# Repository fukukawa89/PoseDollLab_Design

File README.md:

# PoseDoll 人偶硬件设计

通用静态测姿人偶的独立设计仓库；Manny / Quinn 为软件适配目标。原来位于 `DollSimulation` UE 工程中的硬件、固件与硬件诊断工具已经迁入本目录；UE 插件、角色资产与完整 Python 模拟器留在原项目。

## 当前状态

**2026-10-30 O24E 单臂 R5：七自由度测角升级。** 以用户已实装认可摩擦与持姿效果的 R4 为基线，复用六路 O22 MT6701CT 与七颗径向充磁磁铁，腕偏摆增加一路 TMAG5170A1，双轴腕分别测量。保留 R4 摩擦、预紧、防脱结构及 136 件机械五金；重印 P005、P007、P009、P010、P012，复用其余六件主体，新增 29 件传感器附件及 J003/J004 工具。交付打印工程、清单、走线、409 步装配动画、固件和标定工具。数字几何、装配、切片、浏览器与软件检查通过；R5 实物测角精度、走线和升级后的持姿仍待测试，未烧录硬件。

- [R5 打印与装配入口](Hardware/PoseDoll44/bench/revO24E_LArm_Sensing_R5/START_HERE.html) · [重印说明](Hardware/PoseDoll44/bench/revO24E_LArm_Sensing_R5/PRINTING.html)
- [R5 测角方案](Hardware/PoseDoll44/bench/revO24E_LArm_Sensing_R5/SENSING.html) · [逐步装配动画](Hardware/PoseDoll44/bench/revO24E_LArm_Sensing_R5/assembly_guide/index.html) · [验证记录](Hardware/PoseDoll44/bench/revO24E_LArm_Sensing_R5/VERIFICATION.html)
- [R5 完整离线包](Hardware/PoseDoll44/bench/revO24E_LArm_Sensing_R5/O24E_R5_Arm_Sensing_20261030.zip) · [R4 实装反馈](Hardware/PoseDoll44/docs/R4_MECHANICAL_FEEDBACK_20261030.json)

**2026-10-26 O24D 改版交接：** 用户满意当前 O24D 外观，后续保留外观与 UE 骨架，重点重做关节连接、预紧、防松、防脱及装配。T6 W 按用户实装反馈通过；T6 H 按用户依据 T5 安装和 T6 继承关系的判断接受通过，可用于设计推进。T6 R 的整组轴向拔出是已确认缺陷，必须修复。当前 D 的 20 组金属筒输出套还存在规定装入路径与横销干涉，旧球腕入口及机构也需更新。[完整经验、审查与新对话任务](Hardware/PoseDoll44/docs/HANDOFF_O24D_REDESIGN_20261026.zh-CN.md)。本次仅整理与审查，未改动 D/T6 冻结交付包；100 次不补紧目标保留，不虚构循环数据。

**O24C-T6：尼龙锁母防松测试版（以下为发布记录，最新实物反馈见上）。** 针对 T5 H 肩钉逐渐旋退，H、R、双轴腕的七组肩钉统一改用 M3×0.5 DIN985 尼龙锁紧螺母。新一体固定座采用完整六角止转窝和轴向装入，调整内部金属垫圈堆叠，保留原 Φ4×8 / M3×6 肩钉、A8、运动件及 UE 轴心。必须重印 H6-01、R6-01、W6-01，建议先印 C6-01 试配片；其余 10 件打印件与 T5 字节相同。按已备齐 T5 计算，补齐 7 颗锁母、14 片 9×4.3×0.8 平垫和 7 片 7×3.2×0.5 平垫。数字装配、活动采样、切片和教程检查通过；100 次不补紧仍待实测。

- [O24C-T6：打印、装配与测试入口](Hardware/PoseDoll44/bench/revO24C_T6/START_HERE.html)
- [O24C-T6：H 35 步 / R 42 步 / W 74 步逐件动画](Hardware/PoseDoll44/bench/revO24C_T6/tutorial/index.html)
- [O24C-T6：三件重印工程](Hardware/PoseDoll44/bench/revO24C_T6/printing/REPRINT_T6_three_parts.3mf) · [锁母试配片](Hardware/PoseDoll44/bench/revO24C_T6/printing/FIT_T6_locknut_coupon.3mf)
- [O24C-T6：补购与复用清单](Hardware/PoseDoll44/bench/revO24C_T6/HARDWARE.html) · [100 次测试](Hardware/PoseDoll44/bench/revO24C_T6/TEST_PLAN.html)
- [O24C-T6：完整离线包](Hardware/PoseDoll44/bench/revO24C_T6/O24C-T6_print_and_assembly.zip)

**O24C-T5：一体承力座测试版。** 用户实物反馈确认 T3/T4 的 H 摩擦力可用，但 H3-01/02 接缝在强拧和反复摆动后张开。T5 将其合并为 H5-01，同时把 R 固定芯与双轴腕十字芯改成 R5-01、W5-01；五金从侧向导槽装入，保留原有摩擦堆叠和 UE 轴心。仅重印三件，其余 11 个打印件复用，无新增五金规格，省去八组合模五金。旧 H 的反馈仅为定性持姿认可，T5 结构、R/W、磨损和寿命仍需实测。

- [O24C-T5：打印、改动说明与实测](Hardware/PoseDoll44/bench/revO24C_T5/START_HERE.html)
- [O24C-T5：H 29 步 / R 39 步 / W 62 步逐件动画](Hardware/PoseDoll44/bench/revO24C_T5/tutorial/index.html)
- [O24C-T5：三个一体件重印工程](Hardware/PoseDoll44/bench/revO24C_T5/printing/REPRINT_T5_three_parts.3mf)
- [O24C-T5：完整 14 件一盘工程](Hardware/PoseDoll44/bench/revO24C_T5/printing/ALL_H_R_W_T5.3mf)
- [O24C-T5：完整离线包](Hardware/PoseDoll44/bench/revO24C_T5/O24C-T5_print_and_assembly.zip)

**T5 H 最新实测反馈：** 初始摩擦可用，但反复转动十几次后明显衰减。使用普通螺母、没有额外锁固；追加观察发现内侧螺钉尖端从凸出变为缩进，重新拧入约两圈后恢复，强烈支持肩钉旋退为主要原因。当前状态未满足用户“至少活动100次无需补紧”的目标；优先完善独立防松，再验证剩余的沉降、磨损及摩擦变化。[实物反馈与改进要求](Hardware/PoseDoll44/docs/TEST_FEEDBACK_O24C_T5_H.zh-CN.md)。

**O24C-T4：双轴碟簧腕测试版。** 在T3实臂接口上，腕部改回相交双铰链：Y屈伸、随动X偏摆，分别用O22轴肩螺钉和A8预紧。只新增W4-01～04四个打印件；T3的H/R、W3-09掌柄、F3测试附件及C3试片原样复用。E—W仍为80.496305mm。T3球腕未实测，原文件保留供对比；T4持姿与磨损也待实测。新腕约39.6mm横向外廓，独立调摩擦的便利以宽度和更多五金为代价。

- [O24C-T4：打印、装配与五金增量](Hardware/PoseDoll44/bench/revO24C_T4/START_HERE.html)
- [O24C-T4：H 36 步 / R 46 步 / W 76 步逐件动画](Hardware/PoseDoll44/bench/revO24C_T4/tutorial/index.html)
- [已购早期 O22 + T1-S2：T3 / T4 补购对照](Hardware/PoseDoll44/bench/revO24C_T4/HARDWARE.html)
- [O24C-T4：三个样件共 17 件，一盘打印工程](Hardware/PoseDoll44/bench/revO24C_T4/printing/ALL_H_R_W_T4.3mf)
- [O24C-T4：双轴腕三维及逐件定位](Hardware/PoseDoll44/bench/revO24C_T4/viewer/index.html?mode=W)
- [O24C-T4：完整打印测试包](Hardware/PoseDoll44/bench/revO24C_T4/PoseDoll_O24C_T4_Dual_Axis_Wrist_Kit.zip)

**O24C-T3：可按实际骨长联装的肘 H、前臂旋转 R、腕 W 测试模块。** 用户已报告旧 T1 H 持姿不足；T2-H 通用摩擦样条不作为实际手臂的资格验证。T3 在同一组实际零件上借鉴 O22 的轴肩螺钉与 A8 碟簧预紧，E—W 保持 80.496305 mm；腕固定侧球窝与骨杆桥一体，避免整组横向窜动。提供15个关节打印件、4个可拆测试附件、1个试配片及5盘工程。数字装配/姿态/切片检查与实际承载分开记录；实物持姿、磨损、肩部和完整人偶仍待验证。

- [O24C-T3：打印、五金及装配入口](Hardware/PoseDoll44/bench/revO24C_T3/START_HERE.html)
- [O24C-T3：真实尺寸联装和分步定位](Hardware/PoseDoll44/bench/revO24C_T3/viewer/index.html)
- [O24C-T3：完整样件包](Hardware/PoseDoll44/bench/revO24C_T3/PoseDoll_O24C_T3_Arm_Test_Kit.zip)

完整人偶设计交接：[O24D 交接指南](Hardware/PoseDoll44/docs/HANDOFF_O24D.zh-CN.md)。其中原S1测试假设已由2026-10-22的H04实物问题反馈补充；最新T1结构修正见S2重印说明。整机工作以O24D目录最新状态为准。

**O24C-T1-S2：关节台架结构修正版。** 用户实物反馈暴露了H04固定压板的薄弱根部，S2将H04/R04改为连续腹板，并加宽H04/H05/R04/R05的锁轴螺母座及侧向入口。只需重印这四件各1个；其余22件基础件、12件备选件和五金沿用S1。提供四件专用重印盘；完整套件仍为26件基础件、6盘。数字连接/装配/活动/切片检查见交付报告，S2实物刚度、持姿与磨损待测。[S2重印说明](Hardware/PoseDoll44/bench/revO24C_T1/REPRINT_S2.html)。

- [O24C-T1：打印、采购与装配入口](Hardware/PoseDoll44/bench/revO24C_T1/START_HERE.html)
- [O24C-T1：可旋转样件与拆解](Hardware/PoseDoll44/bench/revO24C_T1/preview/index.html)
- [O24C-T1：打印测试包](Hardware/PoseDoll44/bench/revO24C_T1/PoseDoll_O24C_T1_Print_Test_Kit.zip)

**O24C：肩、肘、球面腕的紧凑候选。** 保留 UE 骨架中心和 560 mm 参考比例；相较 B，中立关节包围盒体积分别减少约 9.1%、15.1%、25.5%。标准轴承、主轴径、销径和衬片厚度保留，1,001 组实体动作及选定活动间隙检查通过。可靠性仍需预紧锁固细化和实物验收，A/B 原文件保留。

- [O24C：B / C 同尺度三维对比](Hardware/PoseDoll44/bench/revO24C/preview/index.html)
- [O24C：缩小尺寸、间隙与可靠性取舍](Hardware/PoseDoll44/bench/revO24C/DESIGN.zh-CN.md)

**O24B：新增共心球面手腕研究候选。** 同一个 D24 球形输出件完成两个方向摆动，导向槽限制多余自转；保留 O24A 肩肘和 560 mm 整偶骨架参考。326 个离散姿态通过新腕部干涉检查，磁测角仍需整臂干扰标定，导向间隙、预紧和接口尚未实物验证。B 暂不取代 A。

- [O24B 动画：球体摆动、拆解与 A / B 对比](Hardware/PoseDoll44/bench/revO24B/preview/index.html)
- [O24B 设计、验证结果与制造前条件](Hardware/PoseDoll44/bench/revO24B/DESIGN.zh-CN.md)
- [O24B：9 组机器人方案调研](Hardware/PoseDoll44/bench/revO24B/RESEARCH.zh-CN.md)

**O24A：新增 UE 骨架对齐的左臂数字布局。** 对应 Quinn 560 mm 中立站姿参考高度；肩、肘、腕中心对齐，前臂沿肘—腕线扭转。包含 9 路肩带与手臂测角、可编辑装配、动作预览及独立骨架/网格检查。尚需完善预紧锁固、磁铁杯、线束和实物验收，当前不是可直接打印的制造包。

- [O24A 设计、活动范围与验证边界](Hardware/PoseDoll44/bench/revO24/DESIGN.zh-CN.md)
- [O24A 可摆动三维预览](Hardware/PoseDoll44/bench/revO24/preview/index.html)
- [O24A 手臂动画教程：拆解、旋转与分步装配](Hardware/PoseDoll44/bench/revO24/preview/tutorial.html)
- [O24A 参数化源文件](Hardware/PoseDoll44/cad/revO24/arm.py)
- [O23I 既有整偶设计](Hardware/PoseDoll44/bench/revO23/DESIGN.zh-CN.md)

### O21 历史记录

**O21 已生成约 1500 元的降本工程候选。** 保留 O20 骨架和46路测量；改用 MT6701CT、单面传感板、中央三组16路选择和预制五芯线。单套目标分配1482.50元，尚无正式报价。传感板 ERC/DRC 与固件/主机测试通过；中央板布线、装配集成、实物标定和UE端到端仍未完成，不是整机制造放行。

- [O21设计与成本依据](Hardware/PoseDoll44/docs/DESIGN_REVO21.zh-CN.md)
- [O21预算与通道预览](Hardware/PoseDoll44/tutorials/full-doll-o21/index.html)
- [O21工程设计包](Hardware/PoseDoll44/bench/revO21/PoseDoll_O21_CostDown_Design.zip)
- [加工询价要求](Hardware/PoseDoll44/bench/revO21/RFQ.zh-CN.md)

### O20已保存机械基线

O20为900f572 / posedoll-o20-lightweight-20260930，原ZIP和文件保持不变。保留用户已接受的双髋布局、非相邻姿势避碰及O11摩擦配合结论。

- [O20设计说明](Hardware/PoseDoll44/docs/DESIGN_REVO20.zh-CN.md)
- [O20机械设计包](Hardware/PoseDoll44/bench/revO20/PoseDoll_O20_Universal_Design.zip)

### O19历史记录

**O19 已生成腿杆对齐候选：替换4件腿部连接架，仍为188件/117种打印件。** O11独立小样的配合与可调摩擦已由用户报告通过，不增加摩擦冗余。左大腿及双小腿中间直段对齐参考骨线，右大腿中间段保留向前6mm偏移。双髋中心各外移16mm和既有整机干涉仍保留；24案例及43个中间样本无新增干涉，不能据此声称整机全域通过。

- [O19设计与验证说明](Hardware/PoseDoll44/docs/DESIGN_REVO19.zh-CN.md)
- [O19单台设计包](Hardware/PoseDoll44/bench/revO19/PoseDoll_O19_Universal_Design.zip)
- [O19腿部对照与干涉展示](Hardware/PoseDoll44/tutorials/full-doll-o19/index.html)：本地服务 `/tutorials/full-doll-o19/index.html`。

### O18已保存基线

O18已保存为 `08e8f8b` / `posedoll-o18-prototype-20260930`，342项文件和原ZIP校验通过。以下为O18发布时状态。

**O18 已生成结构简化候选：188件/117种打印件，保留46路测量与USB直连。** 相比O17少14件半壳、28枚螺钉和28枚螺母。O17已冻结为 `5a5ac22` / `posedoll-o17-prototype-20260930`。整机既有干涉仍未解决，先验证Q001/Q002关节小样，不能制造放行。

- [O18设计与已知问题](Hardware/PoseDoll44/docs/DESIGN_REVO18.zh-CN.md)
- [O18简化设计包](Hardware/PoseDoll44/bench/revO18/PoseDoll_O18_Universal_Design.zip)
- [O18三维与外壳对照页](Hardware/PoseDoll44/tutorials/full-doll-o18/index.html)：本地服务 `/tutorials/full-doll-o18/index.html`。

### O17已保存基线

**O17简化候选已冻结：202件/124种打印件。** 保留设计包、三维页面、USB固件与验证报告的原始字节。

- [O17设计与已知问题](Hardware/PoseDoll44/docs/DESIGN_REVO17.zh-CN.md)
- [O17设计包](Hardware/PoseDoll44/bench/revO17/PoseDoll_O17_Universal_Design.zip)
- [O17三维页面](Hardware/PoseDoll44/tutorials/full-doll-o17/index.html)

### O16已保存基线

**O16 单一通用测姿人偶设计候选已冻结保存。** 实体型号收敛为一个，数字高度492.14 mm，46路原始测量；保留O15 Quinn机械几何，不再分别生成两种体型。相邻机构不干涉仍是硬要求，连续全域避碰、实物标定与O16双角色UE验收尚未完成。

- [O16完整设计说明](Hardware/PoseDoll44/docs/DESIGN_REVO16.zh-CN.md)
- [O16单人偶设计包](Hardware/PoseDoll44/bench/revO16/PoseDoll_O16_Universal_Design.zip)：一套打印、采购、线束、实体profile与离线测量参考。
- [O16三维查看页](Hardware/PoseDoll44/tutorials/full-doll-o16/index.html)：先运行下方本地服务，再访问 `/tutorials/full-doll-o16/index.html`。
- 复建与核验脚本：`Hardware/PoseDoll44/cad/revO16/`。本轮不含接触修正，不要求目标角色与实体几何重合。

### O15历史基线

**O15完整数字样机保留，等待实物验证。** 480 mm UE 参考、静态摆姿采集；整机无 1.2 kg 硬门槛，允许手托。采用 FDM 打印与现成金属小件，不需要定制机加工金属件。91 cm 方案继续保留为备用。

- [本次提交与审查入口](Hardware/PoseDoll44/docs/REVIEW_HANDOFF_O15.zh-CN.md)：先读此页，再查详细设计、证据和未验证项。
- [O15 详细审查请求](Hardware/PoseDoll44/docs/REVIEW_REQUEST_REVO15.zh-CN.md)；[数字结果汇总](Hardware/PoseDoll44/generated/revO15/runs/o15_20260929_r1/FINAL_BATCH_SUMMARY.json)。
- [Quinn 统一测试包](Hardware/PoseDoll44/bench/revO15/PoseDoll_O15_Quinn_Prototype.zip) / [Manny 备选包](Hardware/PoseDoll44/bench/revO15/PoseDoll_O15_Manny_Prototype.zip)：只选一套，每套 214 种文件、273 件打印件。
- [中文装配与测试说明](Hardware/PoseDoll44/bench/revO15/guide.html)；[静态采集软件设置](Tools/PoseDollHardwareBridge/README_O15.zh-CN.md)。HTML 请下载打开或通过下方本地服务查看。

本次提交同时收录此前尚未提交的 O5—O14 迭代和 O15 使用的历史依赖。各轮已封存文件保留原字节，旧文档中的“当前”指该轮检查点。O15 的采样几何检查、切片、电路规则、固件构建和 UE 桥接已有数字证据；完整强度、保持力、耐久、带线运动和电子实测仍未完成。

历史入口：[O4](Hardware/PoseDoll44/docs/REVIEW_REQUEST_REVO4.zh-CN.md)、[O3](Hardware/PoseDoll44/docs/START_HERE_REVO3.zh-CN.md)、[O2](Hardware/PoseDoll44/docs/START_HERE_REVO2.zh-CN.md)、[O 初轮](Hardware/PoseDoll44/docs/START_HERE_REVO.zh-CN.md)。不要把历史制造说明与 O15 混用。

以下为备用版的历史基线：

- **机械基线为 Rev N1**：两款分别按 UE 人物参考比例设计，参考身高约 91 cm；胸前大挡板已取消，左肩局部刮碰已修正。
- **下一项为“局部采集 + 外置电源/USB 接口盒”**：方向已确定，新电路板、安装结构和线束尚未实施。
- **小型化仍待比较**：当前尺寸不是已证明的下限，不能直接缩放现有文件，也不能认定重新设计的小型关节必然昂贵。
- 44 个协议槽中，41 轴测量，骨盆 3 轴固定参考；整体位置和全部整体旋转在 UE 调整。
- 当前交付是数字原型候选，尚未实物鉴定。

## 阅读入口

0. [O15历史方案](Hardware/PoseDoll44/docs/REVIEW_HANDOFF_O15.zh-CN.md)。以下 Rev M/N 文档用于备用版。

1. [最新 Rev N1 设计入口](Hardware/PoseDoll44/START_HERE_REVN.zh-CN.md)
2. [胸部修订与设备外置方案](Hardware/PoseDoll44/docs/CHEST_AND_EXTERNAL_REVN.zh-CN.md)
3. [尺寸、磁铁和关节小型化评估](Hardware/PoseDoll44/docs/SIZE_REVIEW_BEFORE_EXTERNAL.zh-CN.md)
4. [制造说明](Hardware/PoseDoll44/docs/FABRICATION_REVM.zh-CN.md)、[装配说明](Hardware/PoseDoll44/docs/ASSEMBLY_REVM.zh-CN.md)、[测试和校准](Hardware/PoseDoll44/docs/BUILD_AND_CALIBRATE_REVM.zh-CN.md)
5. [迁移记录和验证](docs/MIGRATION.zh-CN.md)

Rev M 文档描述原完整基线，使用时应应用 Rev N1 的取消件和左肩修订。更早版本与 `planning/` 是历史依据，不能混作当前制造说明。

## 目录组织

| 路径 | 用途 |
|---|---|
| `Hardware/PoseDoll44/cad/` | 参数化机械模型，保留当前模型仍引用的历史模块 |
| `Hardware/PoseDoll44/electronics/` | 原生 KiCad 工程、符号/封装及板级 STEP 输入 |
| `Hardware/PoseDoll44/mechanical_manifest/` | 轴、接口、比例和网络定义 |
| `Hardware/PoseDoll44/docs/`、`verification/` | 设计说明、数字检查和原型验收依据 |
| `Hardware/PoseDoll44/generated/` | 总装、打印件、查看器、交付清单和本地 CAD 缓存 |
| `Hardware/PoseDoll44/reference/`、`references/` | UE 参考数据及元件资料 |
| `Hardware/PoseDoll44/harness/` | 两款线束与下料表 |
| `Firmware/PoseDollFullBody/` | 六节点完整固件与主机端 C 核心测试 |
| `Firmware/PoseDollHardware/` | 早期单关节固件，历史用途 |
| `Tools/PoseDollHardwareBridge/` | 诊断、校准、数据转换和测试 |
| `Tools/PoseDollSimulator/`、`Shared/` | 硬件需要的协议/运动学代码及配置快照，不含模拟器 GUI |
| `planning/` | 原始规划包副本，父目录中的原下载包也保留 |
| `scripts/` | 独立仓库的检查、构建和查看器入口 |
| `.local/` | 本机迁移清单、运行结果等，不入 Git |

保留 `Hardware/`、`Firmware/`、`Tools/` 层级，以保持已有相对路径及历史资料的可追溯性。协议快照来源与逐文件哈希见 [software_snapshot.json](docs/software_snapshot.json)。

## 环境与离线检查

在本目录打开 PowerShell。本机已经建立独立 `.venv`；新克隆可执行：

```powershell
py -3.13 -m venv .venv
.\.venv\Scripts\python.exe -m pip install -r requirements.txt
.\.venv\Scripts\python.exe scripts/check_repository.py
.\scripts\Build-Design.ps1 -Stage OfflineTests
```

离线检查包括协议配置、Python 测试、C 核心测试和 C/Python 数据帧一致性；不连接硬件或操作 UE。C 测试需要 Visual Studio C 工具链，`-VcVars` 可指定 `vcvars64.bat`。本机迁移后结果为 **81 个 Python 测试、9 个 C 场景通过，数据帧逐字节一致**。

## 打开三维查看器

O15 使用以下命令启动服务，然后访问 `http://127.0.0.1:8769/tutorials/full-doll-o15/index.html`（脚本原来的启动提示仍指向 O14，以此 URL 为准）：

```powershell
python scripts/serve_posedoll_tutorials.py --port 8769
```

提交资料可在新克隆中用 Python 标准库复核：

```powershell
python scripts/verify_o15_review.py
```

以下命令与说明保留为旧版查看器入口：

```powershell
.\scripts\Start-Viewer.ps1
```

默认根据 `verification/revO3/latest.json` 打开 Rev O3 查看器，当前为 `http://127.0.0.1:8874/generated/revO3/runs/o3_20260924_r3/review.html`；通过 `-Revision revN` 打开 91 cm 备用版，仅绑定本机。`-NoBrowser` 只启动服务；端口冲突时可用 `-Port` 指定另一端口，不会自动终止其他进程。

Rev O3 的当前及历史检查运行、HTML、网格、STEP、原生 KiCad 板件、固件产物与原始日志随本次审查提交收录；宿主 C 编译产物通过逐件哈希的 portable ZIP 保存。Rev O 第一轮的 HTML、轻量网格、布局数据及三档关节 STEP 也保留。十份体型布局 STEP 下载需先用 `Build-RevO.ps1 -Stage CAD` 重建。91 cm 备用查看器仍依赖未纳入 Git 的大型网格，需复制旧输出或重建。

## CAD、电路和固件

- CAD：CadQuery 2.7。现有 `Hardware/PoseDoll44/tools/run_cad.py` 可使用本机 CQ-editor 2.7 的环境，需要 CQ-editor 保持开启、Python 版本匹配；也可自行安装常规 CadQuery 环境。
- 电路：KiCad 10，打开 `electronics/` 中对应 `.kicad_pro`。搬迁前已打开的 CQ-editor/KiCad 文件，应从新目录重新打开，避免保存回原路径。
- 固件：ESP-IDF 6.1、ESP32-S3。旧构建缓存已保留，但含旧绝对路径；不要直接在其中增量构建。
- 布线工具：Freerouting 2.4.1 JAR 保留在本机 `Hardware/PoseDoll44/tools/vendor/`，不入 Git；许可证与说明保留。

```powershell
.\scripts\Build-Design.ps1 -Stage CAD
.\scripts\Build-Design.ps1 -Stage Firmware
```

CAD 阶段生成/复核 Rev M 完整基线，耗时较长。Rev N1 的修订脚本位于 `cad/revN/`，依赖 Rev M 完整输出及其复核结果，不是上述命令自动生成的另一套角色。当前源码与必要 CAD 输入纳入 Git。

新构建入口使用本仓库 `.venv`。Firmware 阶段会把检测到旧工程路径的节点缓存移入 `.local/legacy-firmware-builds/` 后重新构建，不删除缓存、不烧录。旧脚本中的 CQ-editor、KiCad、ESP-IDF 安装盘符仍是本机配置；换电脑须配置工具路径，历史工具可参考 `local_toolchain.example.json`。UE 参考重新导出需要原 UE 工程及插件，但导出脚本现在将数据写到本设计仓库。

## Git 与本地成果

Git 收录设计源码、KiCad 工程、固件、必要板级 STEP/角色参考输入、协议快照、说明、交付元数据和检查记录。`.gitattributes` 保留原行尾，避免检出时破坏来源文件的字节哈希。

大型总装 STEP、查看器大网格、CAD 缓存、ESP-IDF 构建目录、Python 环境和第三方工具二进制保留在磁盘，由 `.gitignore` 排除；没有启用 Git LFS。Rev O 审查快照额外收录三档单关节总成 STEP、两个 A 级配合样片 STEP/STL、轻量查看器与本轮原始编译/ERC/DRC 日志，Rev O3 本次另显式收录三个检查运行及其可追溯产物，仍未放开其他版本的整个生成目录。其他机器如需完整本地成果，应另外复制 `Hardware/PoseDoll44/generated/`。**推送 Git 不等于备份全部 6.87 GB 本地成果。**

现有验证报告保留为历史快照，迁移后的路径修复和检查另列记录；没有把迁移当成新一轮全身工程验证。本轮提交由使用者推送到远端；审查应指定 `design/revO-desktop-external` 分支和所读取的完整提交号。

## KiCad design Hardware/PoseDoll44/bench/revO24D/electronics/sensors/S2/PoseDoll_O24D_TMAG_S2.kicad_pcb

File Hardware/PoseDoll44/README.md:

# PoseDoll Manny / Quinn hardware design

[Repository README](../../README.md) · [O24C-T6 test kit](bench/revO24C_T6/START_HERE.html) · [O24D handoff](docs/HANDOFF_O24D.zh-CN.md)

Latest arm test candidate (2026-10-25): O24C-T6. H, R and the two-axis wrist use captured M3 nylon-insert locknuts, retaining all seven O22 shoulder screws. Reprint H6-01/R6-01/W6-01; C6-01 is a recommended fit coupon. Digital checks pass; the 100-cycle no-retightening target remains physically untested. See the repository README for full revision history and the kit for STL, 3MF, assembly and purchasing details.

Historical Rev N1 context: [entry](START_HERE_REVN.zh-CN.md) · [size review](docs/SIZE_REVIEW_BEFORE_EXTERNAL.zh-CN.md). Rev N1 was based on Rev M full body, with the chest facade removed and left shoulder clearance corrected. Its status below is historical and does not describe T6.

CAD source: `cad/revM/final_model.py` plus `cad/revN/chest_clearance.py`. Historical revisions remain because current code and input provenance refer to them. Use revision manifests rather than mixing standalone exports.

This is a digital prototype candidate, not a manufacturing release or a physically qualified product. See the repository README for the migrated layout, toolchain, ignored local exports, offline checks and viewer startup.

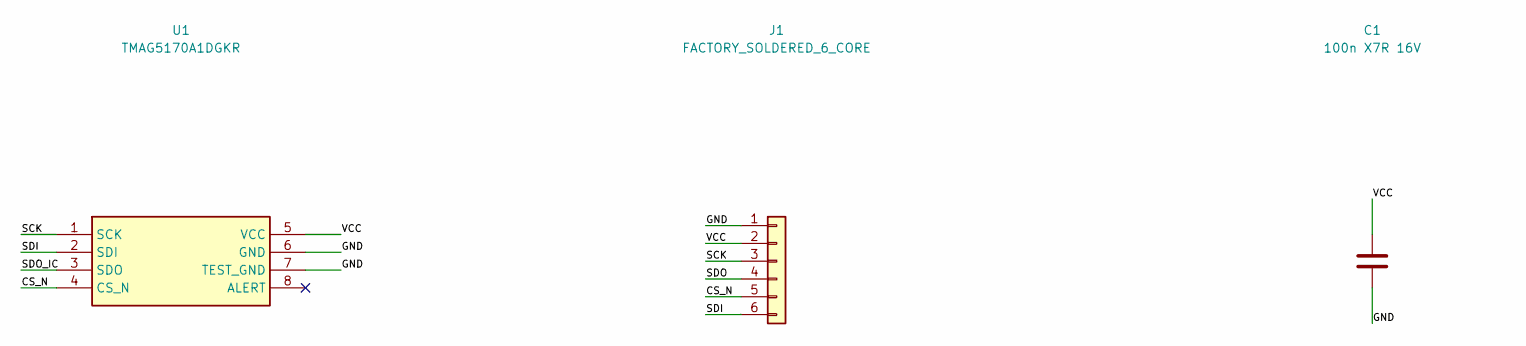
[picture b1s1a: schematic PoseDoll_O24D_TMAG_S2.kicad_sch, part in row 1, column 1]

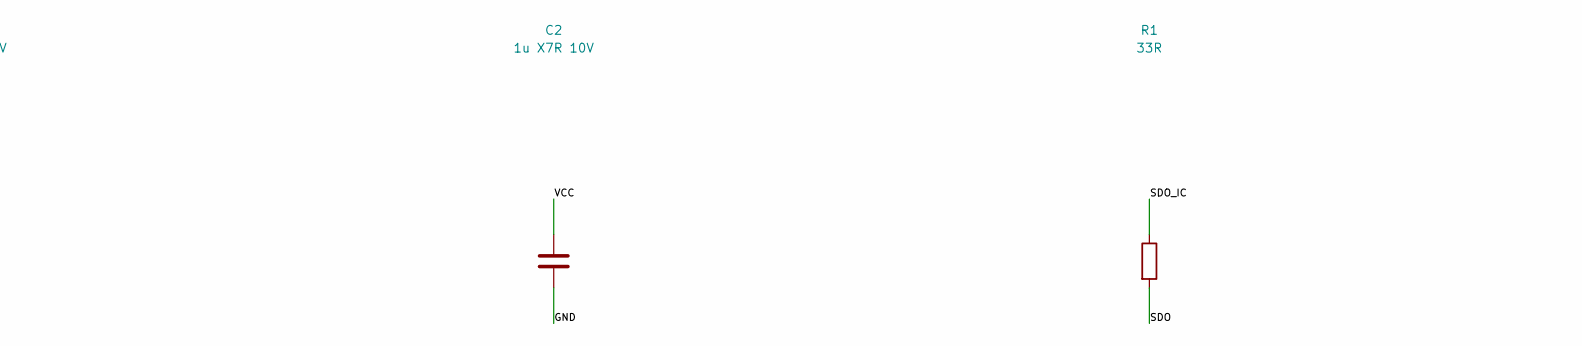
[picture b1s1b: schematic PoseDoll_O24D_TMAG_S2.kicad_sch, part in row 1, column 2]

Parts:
C1: 100n X7R 16V; C_0402_1005Metric
C2: 1u X7R 10V; C_0402_1005Metric
J1: FACTORY_SOLDERED_6_CORE; WirePads_6P
R1: 33R; R_0402_1005Metric
R2: 10k; R_0402_1005Metric
U1: TMAG5170A1DGKR; VSSOP-8_3x3mm_P0.65mm

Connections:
/CS_N: J1.5, R2.2, U1.4 (CS_N)
/GND: C1.2, C2.2, J1.1, U1.6 (GND), U1.7 (TEST_GND)
/SCK: J1.3, U1.1 (SCK)
/SDI: J1.6, U1.2 (SDI)
/SDO: J1.4, R1.2
/SDO_IC: R1.1, U1.3 (SDO)
/VCC: C1.1, C2.1, J1.2, R2.1, U1.5 (VCC)

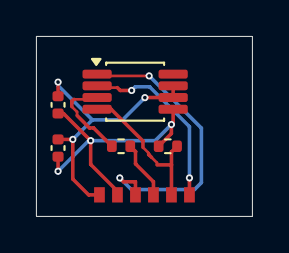
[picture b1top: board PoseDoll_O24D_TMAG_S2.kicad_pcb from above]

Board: 2 copper layers, 12.0 x 10.0 mm, 6 parts (0 on the bottom side), 7 nets.

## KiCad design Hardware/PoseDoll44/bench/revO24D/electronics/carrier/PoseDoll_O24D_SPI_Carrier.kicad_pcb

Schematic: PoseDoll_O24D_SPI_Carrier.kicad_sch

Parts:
C1, C2, C3, C4, C5, C6: 100n; C_0603_1608Metric
C7, C8, C9: 22u 10V X7R effective >=10u; C_0805_2012Metric
C10: 220p C0G starting value; C_0603_1608Metric
D1: SS14 input reverse protection; D_SMA
F4: 1206L110THR / input 1.1A; Fuse_1206_3216Metric
F5: 0467001.NR / 1A fast; Fuse_0603_1608Metric
H1, H2, H3, H4: M2 clearance; MountingHole_2.2mm_M2
J1: XIAO LEFT D0-D6; D2=MOSI; PinHeader_1x07_P2.54mm_Vertical
J2: XIAO_RIGHT D7-D10,3V3,GND,5V NC; PinHeader_1x07_P2.54mm_Vertical
J3: EXTERNAL REGULATED 5V ONLY; NO USB VBUS TIE; JST_PH_B2B-PH-SM4-TB_1x02-1MP_P2.00mm_Vertical
J10: A01 BM06B-SRSS-TB; JST_SH_BM06B-SRSS-TB_1x06-1MP_P1.00mm_Vertical
J11: A02 BM06B-SRSS-TB; JST_SH_BM06B-SRSS-TB_1x06-1MP_P1.00mm_Vertical
J12: A03 BM06B-SRSS-TB; JST_SH_BM06B-SRSS-TB_1x06-1MP_P1.00mm_Vertical
J13: A04 BM06B-SRSS-TB; JST_SH_BM06B-SRSS-TB_1x06-1MP_P1.00mm_Vertical
J14: A05 BM06B-SRSS-TB; JST_SH_BM06B-SRSS-TB_1x06-1MP_P1.00mm_Vertical
J15: A06 BM06B-SRSS-TB; JST_SH_BM06B-SRSS-TB_1x06-1MP_P1.00mm_Vertical
J16: A07 BM06B-SRSS-TB; JST_SH_BM06B-SRSS-TB_1x06-1MP_P1.00mm_Vertical
J17: A08 BM06B-SRSS-TB; JST_SH_BM06B-SRSS-TB_1x06-1MP_P1.00mm_Vertical
J26: B01 BM06B-SRSS-TB; JST_SH_BM06B-SRSS-TB_1x06-1MP_P1.00mm_Vertical
J27: B02 BM06B-SRSS-TB; JST_SH_BM06B-SRSS-TB_1x06-1MP_P1.00mm_Vertical
J28: B03 BM06B-SRSS-TB; JST_SH_BM06B-SRSS-TB_1x06-1MP_P1.00mm_Vertical
J29: B04 BM06B-SRSS-TB; JST_SH_BM06B-SRSS-TB_1x06-1MP_P1.00mm_Vertical
J30: B05 BM06B-SRSS-TB; JST_SH_BM06B-SRSS-TB_1x06-1MP_P1.00mm_Vertical
J31: B06 BM06B-SRSS-TB; JST_SH_BM06B-SRSS-TB_1x06-1MP_P1.00mm_Vertical
J32: B07 BM06B-SRSS-TB; JST_SH_BM06B-SRSS-TB_1x06-1MP_P1.00mm_Vertical
J33: B08 BM06B-SRSS-TB; JST_SH_BM06B-SRSS-TB_1x06-1MP_P1.00mm_Vertical
J34: B09 BM06B-SRSS-TB; JST_SH_BM06B-SRSS-TB_1x06-1MP_P1.00mm_Vertical
J35: B10 BM06B-SRSS-TB; JST_SH_BM06B-SRSS-TB_1x06-1MP_P1.00mm_Vertical
J36: B11 BM06B-SRSS-TB; JST_SH_BM06B-SRSS-TB_1x06-1MP_P1.00mm_Vertical
J37: B12 BM06B-SRSS-TB; JST_SH_BM06B-SRSS-TB_1x06-1MP_P1.00mm_Vertical
J38: B13 BM06B-SRSS-TB; JST_SH_BM06B-SRSS-TB_1x06-1MP_P1.00mm_Vertical
J39: B14 BM06B-SRSS-TB; JST_SH_BM06B-SRSS-TB_1x06-1MP_P1.00mm_Vertical
J40: B15 BM06B-SRSS-TB; JST_SH_BM06B-SRSS-TB_1x06-1MP_P1.00mm_Vertical
J42: C01 BM06B-SRSS-TB; JST_SH_BM06B-SRSS-TB_1x06-1MP_P1.00mm_Vertical
J43: C02 BM06B-SRSS-TB; JST_SH_BM06B-SRSS-TB_1x06-1MP_P1.00mm_Vertical
J44: C03 BM06B-SRSS-TB; JST_SH_BM06B-SRSS-TB_1x06-1MP_P1.00mm_Vertical
J45: C04 BM06B-SRSS-TB; JST_SH_BM06B-SRSS-TB_1x06-1MP_P1.00mm_Vertical
J46: C05 BM06B-SRSS-TB; JST_SH_BM06B-SRSS-TB_1x06-1MP_P1.00mm_Vertical
J47: C06 BM06B-SRSS-TB; JST_SH_BM06B-SRSS-TB_1x06-1MP_P1.00mm_Vertical
J48: C07 BM06B-SRSS-TB; JST_SH_BM06B-SRSS-TB_1x06-1MP_P1.00mm_Vertical
J49: C08 BM06B-SRSS-TB; JST_SH_BM06B-SRSS-TB_1x06-1MP_P1.00mm_Vertical
J50: C09 BM06B-SRSS-TB; JST_SH_BM06B-SRSS-TB_1x06-1MP_P1.00mm_Vertical
J51: C10 BM06B-SRSS-TB; JST_SH_BM06B-SRSS-TB_1x06-1MP_P1.00mm_Vertical
J52: C11 BM06B-SRSS-TB; JST_SH_BM06B-SRSS-TB_1x06-1MP_P1.00mm_Vertical
J53: C12 BM06B-SRSS-TB; JST_SH_BM06B-SRSS-TB_1x06-1MP_P1.00mm_Vertical
J54: C13 BM06B-SRSS-TB; JST_SH_BM06B-SRSS-TB_1x06-1MP_P1.00mm_Vertical
J55: C14 BM06B-SRSS-TB; JST_SH_BM06B-SRSS-TB_1x06-1MP_P1.00mm_Vertical
J56: C15 BM06B-SRSS-TB; JST_SH_BM06B-SRSS-TB_1x06-1MP_P1.00mm_Vertical
L1: 74438357022 / 2.2uH; L_Wuerth_MAPI-4030
Q1: 2N7002; SOT-23
R1, R10, R11, R12, R13, R14, R15, R63: 100k; R_0603_1608Metric
R2, R40, R41, R42: 10k; R_0603_1608Metric
R30, R31, R32, R33, R34, R35: 33R candidate; R_0603_1608Metric
R50: 31.6k 0.1%; R_0603_1608Metric
R51: 6.65k 0.1%; R_0603_1608Metric
R60, R61, R62: 33R; R_0603_1608Metric
TP1: GND; TestPoint_Pad_D1.0mm
TP2: REG_3V45; TestPoint_Pad_D1.0mm
TP3: SENSOR_3V45; TestPoint_Pad_D1.0mm
TP4: VIN; TestPoint_Pad_D1.0mm
U1, U2: SN74LVC244APWR; TSSOP-20_4.4x6.5mm_P0.65mm
U3, U4, U5: CD74HC4067PW; TSSOP-24_4.4x7.8mm_P0.65mm
U6: SN74LVC125APWR; TSSOP-14_4.4x5mm_P0.65mm
U7: AP3429AW5-7; TSOT-23-5

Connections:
/A0: U1.5 (Y6), U3.10 (S0), U4.10 (S0), U5.10 (S0)
/A0_MCU: J1.2, R10.1, U1.15 (A6)
/A1: U1.3 (Y7), U3.11 (S1), U4.11 (S1), U5.11 (S1)
/A01_DO: J10.4, U3.9 (I0)
/A1_MCU: J1.4, R11.1, U1.17 (A7)
/A2: U2.18 (Y0), U3.14 (S2), U4.14 (S2), U5.14 (S2)
/A02_DO: J11.4, U3.8 (I1)
/A2_MCU: J1.5, R12.1, U2.2 (A0)
/A3: U2.16 (Y1), U3.13 (S3), U4.13 (S3), U5.13 (S3)
/A03_DO: J12.4, U3.7 (I2)
/A3_MCU: J1.6, R13.1, U2.4 (A1)
/A04_DO: J13.4, U3.6 (I3)
/A05_DO: J14.4, U3.5 (I4)
/A06_DO: J15.4, U3.4 (I5)
/A07_DO: J16.4, U3.3 (I6)
/A08_DO: J17.4, U3.2 (I7)
/B01_DO: J26.4, U4.9 (I0)
/B02_DO: J27.4, U4.8 (I1)
/B03_DO: J28.4, U4.7 (I2)
/B04_DO: J29.4, U4.6 (I3)
/B05_DO: J30.4, U4.5 (I4)
/B06_DO: J31.4, U4.4 (I5)
/B07_DO: J32.4, U4.3 (I6)
/B08_DO: J33.4, U4.2 (I7)
/B09_DO: J34.4, U4.23 (I8)
/B10_DO: J35.4, U4.22 (I9)
/B11_DO: J36.4, U4.21 (I10)
/B12_DO: J37.4, U4.20 (I11)
/B13_DO: J38.4, U4.19 (I12)
/B14_DO: J39.4, U4.18 (I13)
/B15_DO: J40.4, U4.17 (I14)
/C01_DO: J42.4, U5.9 (I0)
/C02_DO: J43.4, U5.8 (I1)
/C03_DO: J44.4, U5.7 (I2)
/C04_DO: J45.4, U5.6 (I3)
/C05_DO: J46.4, U5.5 (I4)
/C06_DO: J47.4, U5.4 (I5)
/C07_DO: J48.4, U5.3 (I6)
/C08_DO: J49.4, U5.2 (I7)
/C09_DO: J50.4, U5.23 (I8)
/C10_DO: J51.4, U5.22 (I9)
/C11_DO: J52.4, U5.21 (I10)
/C12_DO: J53.4, U5.20 (I11)
/C13_DO: J54.4, U5.19 (I12)
/C14_DO: J55.4, U5.18 (I13)
/C15_DO: J56.4, U5.17 (I14)
/CLK_A: J10.3, J11.3, J12.3, J13.3, J14.3, J15.3, J16.3, J17.3, R30.2
/CLK_A_DRV: R30.1, U1.18 (Y0)
/CLK_B: J26.3, J27.3, J28.3, J29.3, J30.3, J31.3, J32.3, J33.3, J34.3, J35.3, J36.3, J37.3, J38.3, J39.3, J40.3, R32.2
/CLK_B_DRV: R32.1, U1.16 (Y1)
/CLK_C: J42.3, J43.3, J44.3, J45.3, J46.3, J47.3, J48.3, J49.3, J50.3, J51.3, J52.3, J53.3, J54.3, J55.3, J56.3, R34.2
/CLK_C_DRV: R34.1, U1.14 (Y2)
/CLK_MCU: J2.2, R14.1, U1.2 (A0), U1.4 (A1), U1.6 (A2)
/CS_A: J10.5, J11.5, J12.5, J13.5, J14.5, J15.5, J16.5, J17.5, R31.2
/CS_A_DRV: R31.1, U1.12 (Y3)
/CS_B: J26.5, J27.5, J28.5, J29.5, J30.5, J31.5, J32.5, J33.5, J34.5, J35.5, J36.5, J37.5, J38.5, J39.5, J40.5, R33.2
/CS_B_DRV: R33.1, U1.9 (Y4)
/CS_C: J42.5, J43.5, J44.5, J45.5, J46.5, J47.5, J48.5, J49.5, J50.5, J51.5, J52.5, J53.5, J54.5, J55.5, J56.5, R35.2
/CS_C_DRV: R35.1, U1.7 (Y5)
/CS_MCU: J1.7, R15.1, U1.8 (A3), U1.11 (A4), U1.13 (A5)
/DO_A: R40.1, U3.1 (COM), U6.2 (A1)
/DO_A_MCU: J2.3, U6.3 (Y1)
/DO_B: R41.1, U4.1 (COM), U6.5 (A2)
/DO_B_MCU: J2.4, U6.6 (Y2)
/DO_C: R42.1, U5.1 (COM), U6.9 (A3)
/DO_C_MCU: J2.1, U6.8 (Y3)
/ENABLE_N: Q1.3 (D), R2.1, U1.1 (OE1_N), U1.19 (OE2_N), U2.1 (OE1_N), U2.19 (OE2_N), U3.15 (E), U4.15 (E), U5.15 (E)
/EN_MCU: J1.1, Q1.1 (G), R1.1
/EXT5V: F4.1, J3.1
/FB: C10.2, R50.2, R51.1, U7.5 (FB)
/FUSED5V: D1.2 (A), F4.2
/GND: C1.2, C2.2, C3.2, C4.2, C5.2, C6.2, C7.2, C8.2, C9.2, J2.6, J3.2, J10.1, J11.1, J12.1, J13.1, J14.1, J15.1, J16.1, J17.1, J26.1, J27.1, J28.1, J29.1, J30.1, J31.1, J32.1, J33.1, J34.1, J35.1, J36.1, J37.1, J38.1, J39.1, J40.1, J42.1, J43.1, J44.1, J45.1, J46.1, J47.1, J48.1, J49.1, J50.1, J51.1, J52.1, J53.1, J54.1, J55.1, J56.1, Q1.2 (S), R1.2, R10.2, R11.2, R12.2, R13.2, R14.2, R15.2, R51.2, R63.2, TP1.1, U1.10 (GND), U2.10 (GND), U2.13 (A5), U2.15 (A6), U2.17 (A7), U3.12 (GND), U3.16 (I15), U3.17 (I14), U3.18 (I13), U3.19 (I12), U3.20 (I11), U3.21 (I10), U3.22 (I9), U3.23 (I8), U4.12 (GND), U4.16 (I15), U5.12 (GND), U5.16 (I15), U6.1 (OE1_N), U6.4 (OE2_N)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
/LX: L1.1, U7.3 (LX)
/MCU_3V3: C6.1, J2.5, U6.13 (OE4_N), U6.14 (VCC)
/MOSI_A: J10.6, J11.6, J12.6, J13.6, J14.6, J15.6, J16.6, J17.6, R60.2
/MOSI_A_DRV: R60.1, U2.14 (Y2)
/MOSI_B: J26.6, J27.6, J28.6, J29.6, J30.6, J31.6, J32.6, J33.6, J34.6, J35.6, J36.6, J37.6, J38.6, J39.6, J40.6, R61.2
/MOSI_B_DRV: R61.1, U2.12 (Y3)
/MOSI_C: J42.6, J43.6, J44.6, J45.6, J46.6, J47.6, J48.6, J49.6, J50.6, J51.6, J52.6, J53.6, J54.6, J55.6, J56.6, R62.2
/MOSI_C_DRV: R62.1, U2.9 (Y4)
/MOSI_MCU: J1.3, R63.1, U2.6 (A2), U2.8 (A3), U2.11 (A4)
/REG_3V45: C8.1, C9.1, C10.1, F5.1, L1.2, R50.1, TP2.1
/SENSOR_3V45: C1.1, C2.1, C3.1, C4.1, C5.1, F5.2, J10.2, J11.2, J12.2, J13.2, J14.2, J15.2, J16.2, J17.2, J26.2, J27.2, J28.2, J29.2, J30.2, J31.2, J32.2, J33.2, J34.2, J35.2, J36.2, J37.2, J38.2, J39.2, J40.2, J42.2, J43.2, J44.2, J45.2, J46.2, J47.2, J48.2, J49.2, J50.2, J51.2, J52.2, J53.2, J54.2, J55.2, J56.2, R2.2, R40.2, R41.2, R42.2, TP3.1, U1.20 (VCC), U2.20 (VCC), U3.24 (VCC), U4.24 (VCC), U5.24 (VCC)
/VIN: C7.1, D1.1 (K), TP4.1, U7.1 (EN), U7.4 (VIN)

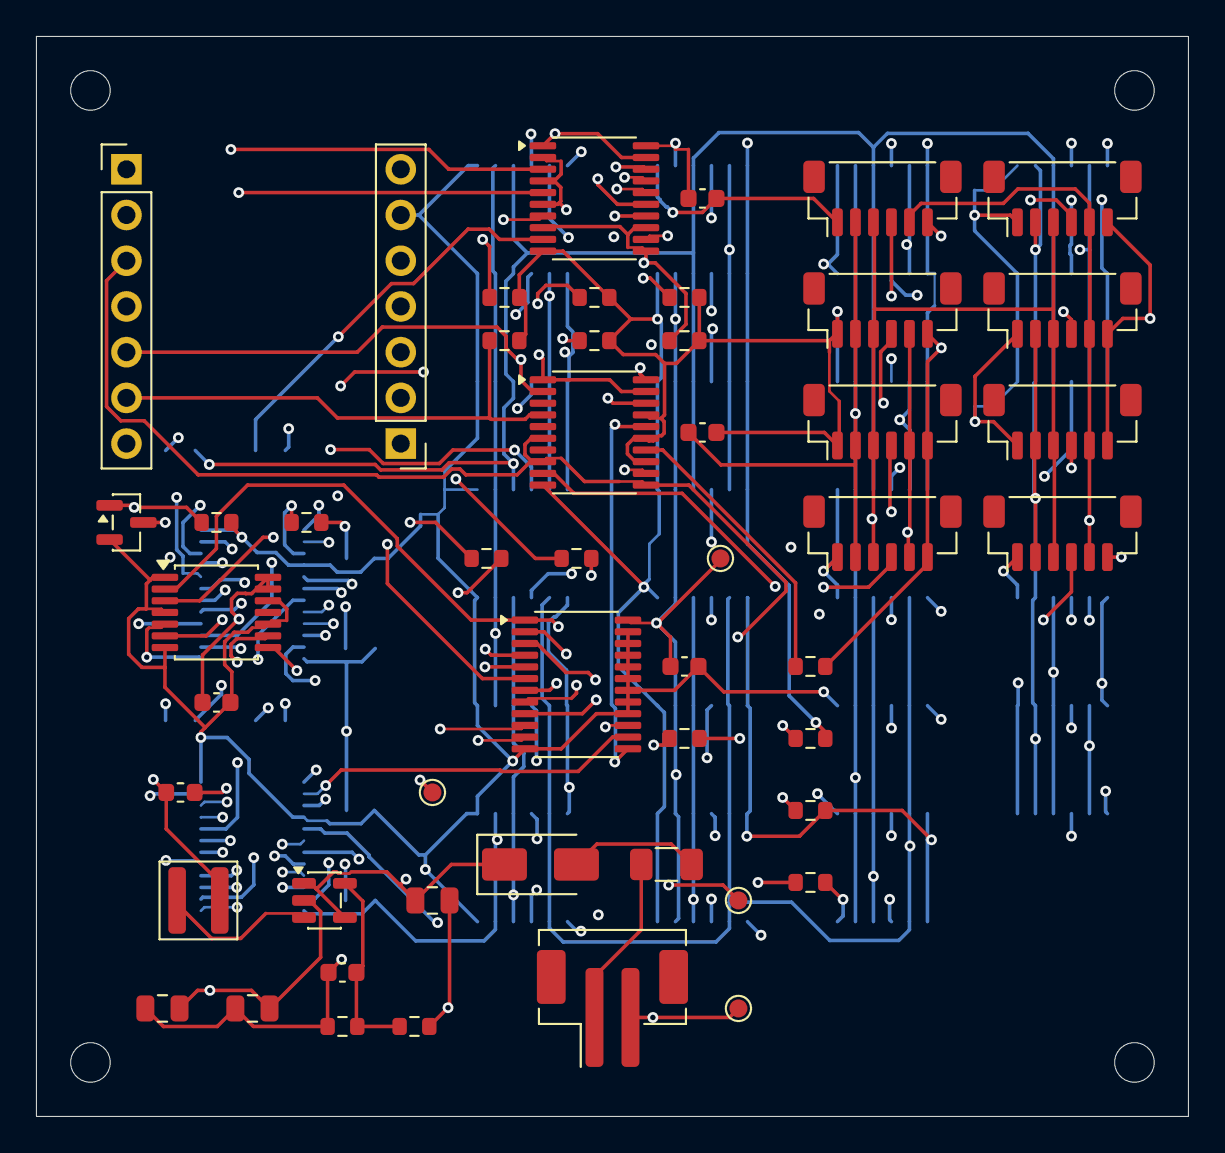
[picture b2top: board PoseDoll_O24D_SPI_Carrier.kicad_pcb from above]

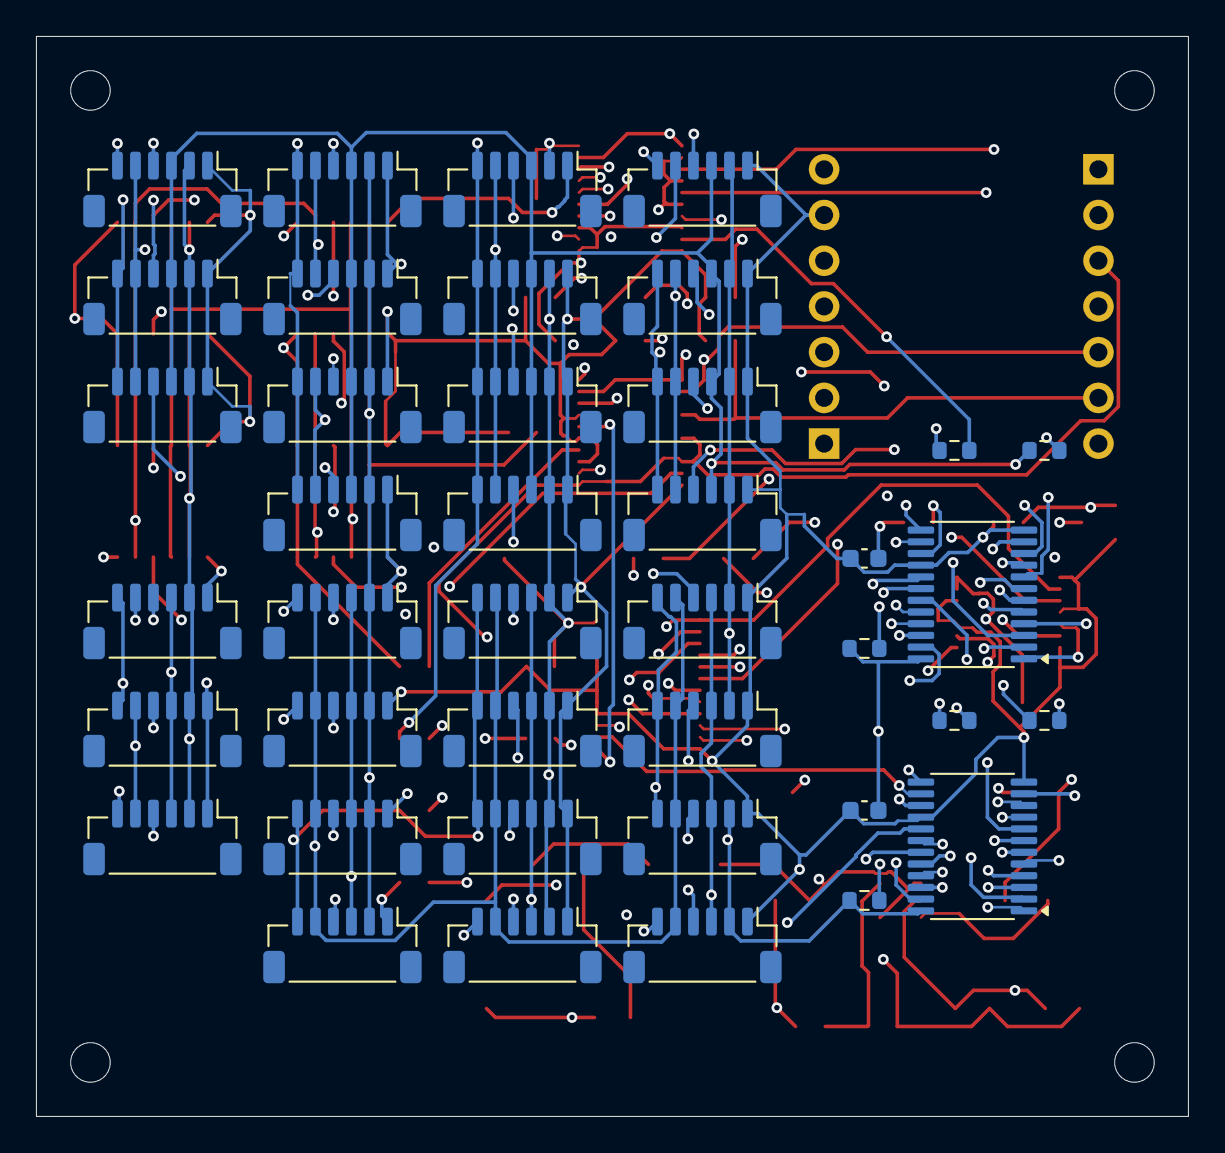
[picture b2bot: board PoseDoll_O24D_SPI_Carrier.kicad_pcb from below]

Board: 4 copper layers, 64.0 x 60.0 mm, 94 parts (40 on the bottom side), 84 nets.

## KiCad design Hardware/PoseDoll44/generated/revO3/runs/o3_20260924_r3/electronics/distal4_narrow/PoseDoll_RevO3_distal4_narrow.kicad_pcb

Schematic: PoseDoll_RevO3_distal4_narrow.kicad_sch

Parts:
C26, C27, C28, C29: 100n X7R; C_0603_1608Metric
C50: 1u X7R; C_0603_1608Metric
J16: P6 sensor / CS GPIO8; JST_SH_BM06B-SRSS-TB_1x06-1MP_P1.00mm_Vertical
J17: P7 sensor / CS GPIO9; JST_SH_BM06B-SRSS-TB_1x06-1MP_P1.00mm_Vertical
J18: P8 sensor / CS GPIO10; JST_SH_BM06B-SRSS-TB_1x06-1MP_P1.00mm_Vertical
J19: P9 sensor / CS GPIO14; JST_SH_BM06B-SRSS-TB_1x06-1MP_P1.00mm_Vertical
J50: BM14B-SRSS-TB / SHR-14V-S / SSH-003T-P0.2-H; JST_SH_BM14B-SRSS-TB_1x14-1MP_P1.00mm_Vertical
R160, R161, R162, R170, R171, R172, R180, R181, R182, R190, R191, R192: 100R; R_0603_1608Metric
R163, R167, R173, R177, R183, R187, R193, R197: 10k; R_0603_1608Metric
R164, R165, R174, R175, R184, R185, R194, R195: 47k; R_0603_1608Metric
R166, R176, R186, R196: 100k; R_0603_1608Metric
R500: 100R return source damping candidate; R_0603_1608Metric
U16, U17, U18, U19: SN74LVC125ABQAR; DHWQFN-14-1EP_2.5x3mm_P0.5mm_EP1x1.5mm

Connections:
/+3V3: C26.1, C27.1, C28.1, C29.1, C50.1, J16.2, J17.2, J18.2, J19.2, J50.13, J50.14, R163.1, R167.1, R173.1, R177.1, R183.1, R187.1, R193.1, R197.1, U16.14 (VCC), U17.14 (VCC), U18.14 (VCC), U19.14 (VCC)
/CS6_REMOTE: J50.7, R163.2, U16.1 (1OE_N), U16.4 (2OE_N), U16.10 (3OE_N), U16.12 (4A)
/CS7_REMOTE: J50.8, R173.2, U17.1 (1OE_N), U17.4 (2OE_N), U17.10 (3OE_N), U17.12 (4A)
/CS8_REMOTE: J50.10, R183.2, U18.1 (1OE_N), U18.4 (2OE_N), U18.10 (3OE_N), U18.12 (4A)
/CS9_REMOTE: J50.11, R193.2, U19.1 (1OE_N), U19.4 (2OE_N), U19.10 (3OE_N), U19.12 (4A)
/GND: C26.2, C27.2, C28.2, C29.2, C50.2, J16.1, J17.1, J18.1, J19.1, J50.1, J50.3, J50.5, J50.9, J50.12, R164.2, R165.2, R166.2, R174.2, R175.2, R176.2, R184.2, R185.2, R186.2, R194.2, R195.2, R196.2, U16.7 (GND), U16.13 (4OE_N), U16.15 (EP_GND), U17.7 (GND), U17.13 (4OE_N), U17.15 (EP_GND), U18.7 (GND), U18.13 (4OE_N), U18.15 (EP_GND), U19.7 (GND), U19.13 (4OE_N), U19.15 (EP_GND)
/LINK_MISO: J50.6, R500.2
/LINK_MOSI: J50.4, U16.5 (2A), U17.5 (2A), U18.5 (2A), U19.5 (2A)
/LINK_SCK: J50.2, U16.2 (1A), U17.2 (1A), U18.2 (1A), U19.2 (1A)
/MISO_REMOTE_DRV: R500.1, U16.8 (3Y), U17.8 (3Y), U18.8 (3Y), U19.8 (3Y)
/P6_CS: J16.6, R162.2, R167.2
/P6_CS_DRV: R162.1, U16.11 (4Y)
/P6_MISO: J16.5, R166.1, U16.9 (3A)
/P6_MOSI: J16.4, R161.2, R165.1
/P6_MOSI_DRV: R161.1, U16.6 (2Y)
/P6_SCK: J16.3, R160.2, R164.1
/P6_SCK_DRV: R160.1, U16.3 (1Y)
/P7_CS: J17.6, R172.2, R177.2
/P7_CS_DRV: R172.1, U17.11 (4Y)
/P7_MISO: J17.5, R176.1, U17.9 (3A)
/P7_MOSI: J17.4, R171.2, R175.1
/P7_MOSI_DRV: R171.1, U17.6 (2Y)
/P7_SCK: J17.3, R170.2, R174.1
/P7_SCK_DRV: R170.1, U17.3 (1Y)
/P8_CS: J18.6, R182.2, R187.2
/P8_CS_DRV: R182.1, U18.11 (4Y)
/P8_MISO: J18.5, R186.1, U18.9 (3A)
/P8_MOSI: J18.4, R181.2, R185.1
/P8_MOSI_DRV: R181.1, U18.6 (2Y)
/P8_SCK: J18.3, R180.2, R184.1
/P8_SCK_DRV: R180.1, U18.3 (1Y)
/P9_CS: J19.6, R192.2, R197.2
/P9_CS_DRV: R192.1, U19.11 (4Y)
/P9_MISO: J19.5, R196.1, U19.9 (3A)
/P9_MOSI: J19.4, R191.2, R195.1
/P9_MOSI_DRV: R191.1, U19.6 (2Y)
/P9_SCK: J19.3, R190.2, R194.1
/P9_SCK_DRV: R190.1, U19.3 (1Y)

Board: 4 copper layers, 47 parts (42 on the bottom side), 38 nets, no tracks yet.

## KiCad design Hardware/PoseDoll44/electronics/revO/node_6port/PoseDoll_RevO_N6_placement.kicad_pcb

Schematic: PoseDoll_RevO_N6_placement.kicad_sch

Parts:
C1: 10u X5R 25V / CL21A106KAYNNNE; C_0805_2012Metric
C2, C4: 22u X5R 16V / CL21A226MOYNNNE; C_0805_2012Metric
C3, C5, C7, C21, C22, C23, C24, C25, C26: 100n X7R; C_0603_1608Metric
C6: 1u X7R; C_0603_1608Metric
D1: PESD5V0S2BT,215; SOT-23
J1: Fused 5V branch; NOT 12V qualified; JST_PH_B2B-PH-SM4-TB_1x02-1MP_P2.00mm_Vertical
J2: CAN IN / GND-L-H; JST_GH_BM03B-GHS-TBT_1x03-1MP_P1.25mm_Vertical
J3: CAN OUT / GND-L-H; JST_GH_BM03B-GHS-TBT_1x03-1MP_P1.25mm_Vertical
J11: P1 sensor / CS GPIO2; JST_SH_BM06B-SRSS-TB_1x06-1MP_P1.00mm_Vertical
J12: P2 sensor / CS GPIO4; JST_SH_BM06B-SRSS-TB_1x06-1MP_P1.00mm_Vertical
J13: P3 sensor / CS GPIO5; JST_SH_BM06B-SRSS-TB_1x06-1MP_P1.00mm_Vertical
J14: P4 sensor / CS GPIO6; JST_SH_BM06B-SRSS-TB_1x06-1MP_P1.00mm_Vertical
J15: P5 sensor / CS GPIO7; JST_SH_BM06B-SRSS-TB_1x06-1MP_P1.00mm_Vertical
J16: P6 sensor / CS GPIO8; JST_SH_BM06B-SRSS-TB_1x06-1MP_P1.00mm_Vertical
JP1: CAN TERM: close endpoints only; SolderJumper-2_P1.3mm_Open_Pad1.0x1.5mm
L1: LSXND4040TKL2R2MDG / 2.2uH; L_Taiyo-Yuden_NR-40xx
R1, R2, R4, R113, R117, R123, R127, R133, R137, R143, R147, R153, R157, R163, R167: 10k; R_0603_1608Metric
R3, R116, R126, R136, R146, R156, R166: 100k; R_0603_1608Metric
R5: 120R 1% 0.33W / CRCW0603120RFKEAHP; R_0603_1608Metric
R110, R111, R112, R120, R121, R122, R130, R131, R132, R140, R141, R142, R150, R151, R152, R160, R161, R162: 100R; R_0603_1608Metric
R114, R115, R124, R125, R134, R135, R144, R145, R154, R155, R164, R165: 47k; R_0603_1608Metric
TP1: UART_TX; TestPoint_Pad_D1.0mm
TP2: UART_RX; TestPoint_Pad_D1.0mm
TP3: GND; TestPoint_Pad_D1.0mm
TP4: PG; TestPoint_Pad_D1.0mm
TP5: EN; TestPoint_Pad_D1.0mm
TP6: BOOT_N; TestPoint_Pad_D1.0mm
U1: ESP32-S3-WROOM-1-N8; ESP32-S3-WROOM-1
U2: TPS62162DSGR; Texas_DSG0008A_WSON-8-1EP_2x2mm_P0.5mm_EP0.9x1.6mm
U3: TCAN332DR; SOIC-8_3.9x4.9mm_P1.27mm
U11, U12, U13, U14, U15, U16: SN74LVC125APWR; TSSOP-14_4.4x5mm_P0.65mm

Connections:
/+3V3: C2.1, C4.1, C5.1, C7.1, C21.1, C22.1, C23.1, C24.1, C25.1, C26.1, J11.2, J12.2, J13.2, J14.2, J15.2, J16.2, L1.2, R1.1, R2.1, R3.1, R4.1, R113.1, R117.1, R123.1, R127.1, R133.1, R137.1, R143.1, R147.1, R153.1, R157.1, R163.1, R167.1, U1.2 (3V3), U2.6 (VOS), U3.3 (VCC), U11.14 (VCC), U12.14 (VCC), U13.14 (VCC), U14.14 (VCC), U15.14 (VCC), U16.14 (VCC)
/+5V_IN: C1.1, C3.1, J1.1, U2.2 (VIN), U2.3 (EN)
/BOOT_N: R2.2, TP6.1, U1.27 (IO0)
/CAN_H: D1.2 (CAN2), J2.3, J3.3, R5.1, U3.7 (CANH)
/CAN_L: D1.1 (CAN1), J2.2, J3.2, JP1.2 (B), U3.6 (CANL)
/CAN_RX: U1.11 (IO18), U3.4 (RXD)
/CAN_TX: R4.2, U1.10 (IO17), U3.1 (TXD)
/CS1_MCU: R113.2, U1.38 (IO2), U11.1 (1OE_N), U11.4 (2OE_N), U11.10 (3OE_N), U11.12 (4A)
/CS2_MCU: R123.2, U1.4 (IO4), U12.1 (1OE_N), U12.4 (2OE_N), U12.10 (3OE_N), U12.12 (4A)
/CS3_MCU: R133.2, U1.5 (IO5), U13.1 (1OE_N), U13.4 (2OE_N), U13.10 (3OE_N), U13.12 (4A)
/CS4_MCU: R143.2, U1.6 (IO6), U14.1 (1OE_N), U14.4 (2OE_N), U14.10 (3OE_N), U14.12 (4A)
/CS5_MCU: R153.2, U1.7 (IO7), U15.1 (1OE_N), U15.4 (2OE_N), U15.10 (3OE_N), U15.12 (4A)
/CS6_MCU: R163.2, U1.12 (IO8), U16.1 (1OE_N), U16.4 (2OE_N), U16.10 (3OE_N), U16.12 (4A)
/EN: C6.1, R1.2, TP5.1, U1.3 (EN)
/GND: C1.2, C2.2, C3.2, C4.2, C5.2, C6.2, C7.2, C21.2, C22.2, C23.2, C24.2, C25.2, C26.2, D1.3 (GND), J1.2, J2.1, J3.1, J11.1, J12.1, J13.1, J14.1, J15.1, J16.1, R114.2, R115.2, R116.2, R124.2, R125.2, R126.2, R134.2, R135.2, R136.2, R144.2, R145.2, R146.2, R154.2, R155.2, R156.2, R164.2, R165.2, R166.2, TP3.1, U1.1 (GND), U1.40 (GND), U1.41 (GND), U2.1 (PGND), U2.4 (AGND), U2.5 (FB), U2.9 (PAD), U3.2 (GND), U11.7 (GND), U11.13 (4OE_N), U12.7 (GND), U12.13 (4OE_N), U13.7 (GND), U13.13 (4OE_N), U14.7 (GND), U14.13 (4OE_N), U15.7 (GND), U15.13 (4OE_N), U16.7 (GND), U16.13 (4OE_N)
/P1_CS: J11.6, R112.2, R117.2
/P1_CS_DRV: R112.1, U11.11 (4Y)
/P1_MISO: J11.5, R116.1, U11.9 (3A)
/P1_MOSI: J11.4, R111.2, R115.1
/P1_MOSI_DRV: R111.1, U11.6 (2Y)
/P1_SCK: J11.3, R110.2, R114.1
/P1_SCK_DRV: R110.1, U11.3 (1Y)
/P2_CS: J12.6, R122.2, R127.2
/P2_CS_DRV: R122.1, U12.11 (4Y)
/P2_MISO: J12.5, R126.1, U12.9 (3A)
/P2_MOSI: J12.4, R121.2, R125.1
/P2_MOSI_DRV: R121.1, U12.6 (2Y)
/P2_SCK: J12.3, R120.2, R124.1
/P2_SCK_DRV: R120.1, U12.3 (1Y)
/P3_CS: J13.6, R132.2, R137.2
/P3_CS_DRV: R132.1, U13.11 (4Y)
/P3_MISO: J13.5, R136.1, U13.9 (3A)
/P3_MOSI: J13.4, R131.2, R135.1
/P3_MOSI_DRV: R131.1, U13.6 (2Y)
/P3_SCK: J13.3, R130.2, R134.1
/P3_SCK_DRV: R130.1, U13.3 (1Y)
/P4_CS: J14.6, R142.2, R147.2
/P4_CS_DRV: R142.1, U14.11 (4Y)
/P4_MISO: J14.5, R146.1, U14.9 (3A)
/P4_MOSI: J14.4, R141.2, R145.1
/P4_MOSI_DRV: R141.1, U14.6 (2Y)
/P4_SCK: J14.3, R140.2, R144.1
/P4_SCK_DRV: R140.1, U14.3 (1Y)
/P5_CS: J15.6, R152.2, R157.2
/P5_CS_DRV: R152.1, U15.11 (4Y)
/P5_MISO: J15.5, R156.1, U15.9 (3A)
/P5_MOSI: J15.4, R151.2, R155.1
/P5_MOSI_DRV: R151.1, U15.6 (2Y)
/P5_SCK: J15.3, R150.2, R154.1
/P5_SCK_DRV: R150.1, U15.3 (1Y)
/P6_CS: J16.6, R162.2, R167.2
/P6_CS_DRV: R162.1, U16.11 (4Y)
/P6_MISO: J16.5, R166.1, U16.9 (3A)
/P6_MOSI: J16.4, R161.2, R165.1
/P6_MOSI_DRV: R161.1, U16.6 (2Y)
/P6_SCK: J16.3, R160.2, R164.1
/P6_SCK_DRV: R160.1, U16.3 (1Y)
/PG: R3.2, TP4.1, U2.8 (PG)
/SPI_MISO: U1.21 (IO13), U11.8 (3Y), U12.8 (3Y), U13.8 (3Y), U14.8 (3Y), U15.8 (3Y), U16.8 (3Y)
/SPI_MOSI: U1.19 (IO11), U11.5 (2A), U12.5 (2A), U13.5 (2A), U14.5 (2A), U15.5 (2A), U16.5 (2A)
/SPI_SCK: U1.20 (IO12), U11.2 (1A), U12.2 (1A), U13.2 (1A), U14.2 (1A), U15.2 (1A), U16.2 (1A)
/SW_BUCK: L1.1, U2.7 (SW)
/TERM_R: JP1.1 (A), R5.2
/UART_RX: TP2.1, U1.36 (RXD0)
/UART_TX: TP1.1, U1.37 (TXD0)

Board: 4 copper layers, 93 parts (47 on the bottom side), 65 nets, no tracks yet.

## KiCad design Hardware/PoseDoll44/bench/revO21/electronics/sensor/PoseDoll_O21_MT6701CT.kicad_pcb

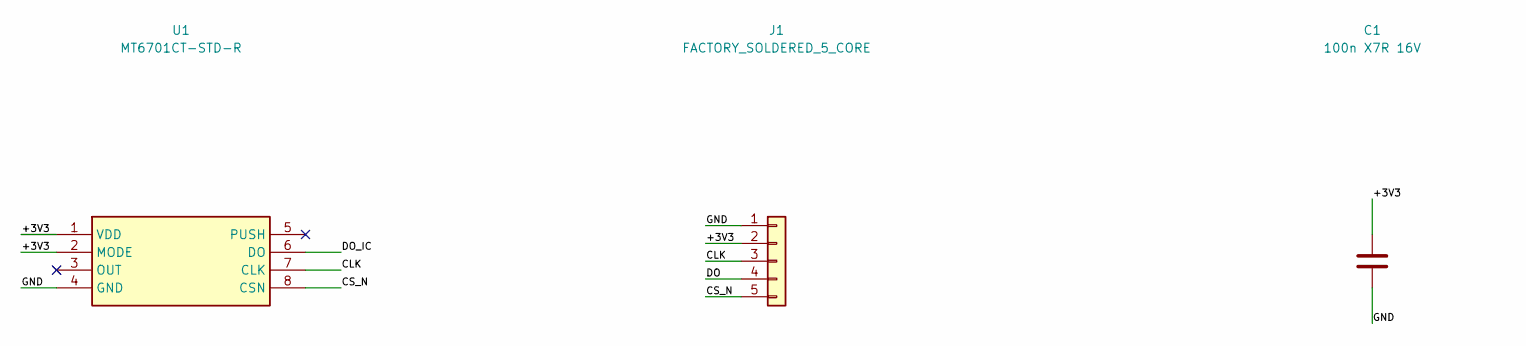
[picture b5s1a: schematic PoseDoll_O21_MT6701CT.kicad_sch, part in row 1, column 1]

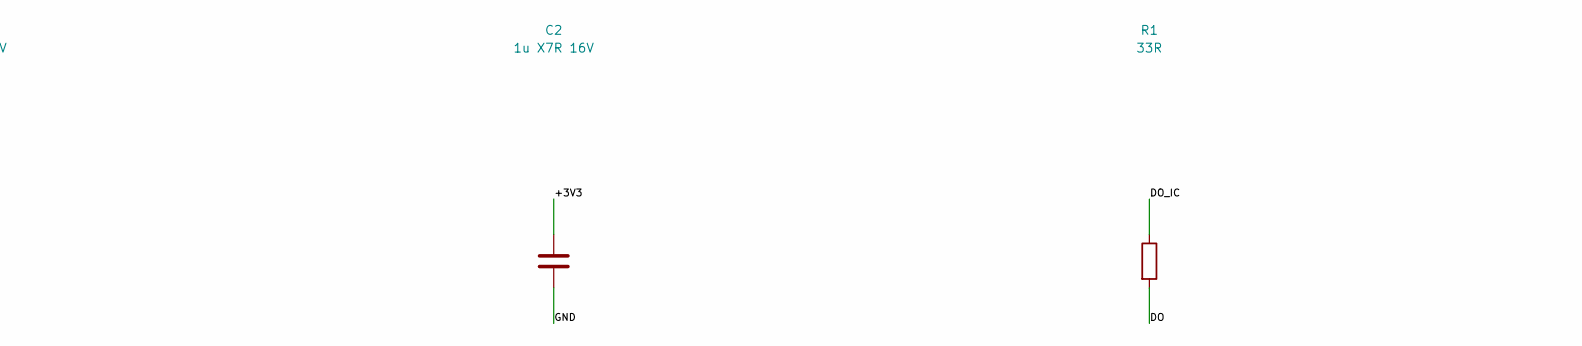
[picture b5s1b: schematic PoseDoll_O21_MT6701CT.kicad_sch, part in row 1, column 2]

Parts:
C1: 100n X7R 16V; C_0603_1608Metric
C2: 1u X7R 16V; C_0603_1608Metric
J1: FACTORY_SOLDERED_5_CORE; WirePads_5P
R1: 33R; R_0603_1608Metric
R2: 10k; R_0603_1608Metric
U1: MT6701CT-STD-R; SOIC-8_3.9x4.9mm_P1.27mm

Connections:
/+3V3: C1.1, C2.1, J1.2, R2.1, U1.1 (VDD), U1.2 (MODE)
/CLK: J1.3, U1.7 (CLK)
/CS_N: J1.5, R2.2, U1.8 (CSN)
/DO: J1.4, R1.2
/DO_IC: R1.1, U1.6 (DO)
/GND: C1.2, C2.2, J1.1, U1.4 (GND)

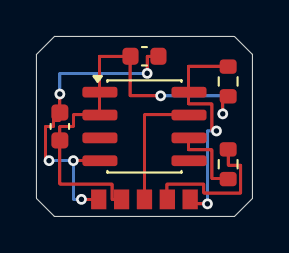
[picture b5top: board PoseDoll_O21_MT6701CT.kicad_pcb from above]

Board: 2 copper layers, 12.0 x 10.0 mm, 6 parts (0 on the bottom side), 6 nets.
